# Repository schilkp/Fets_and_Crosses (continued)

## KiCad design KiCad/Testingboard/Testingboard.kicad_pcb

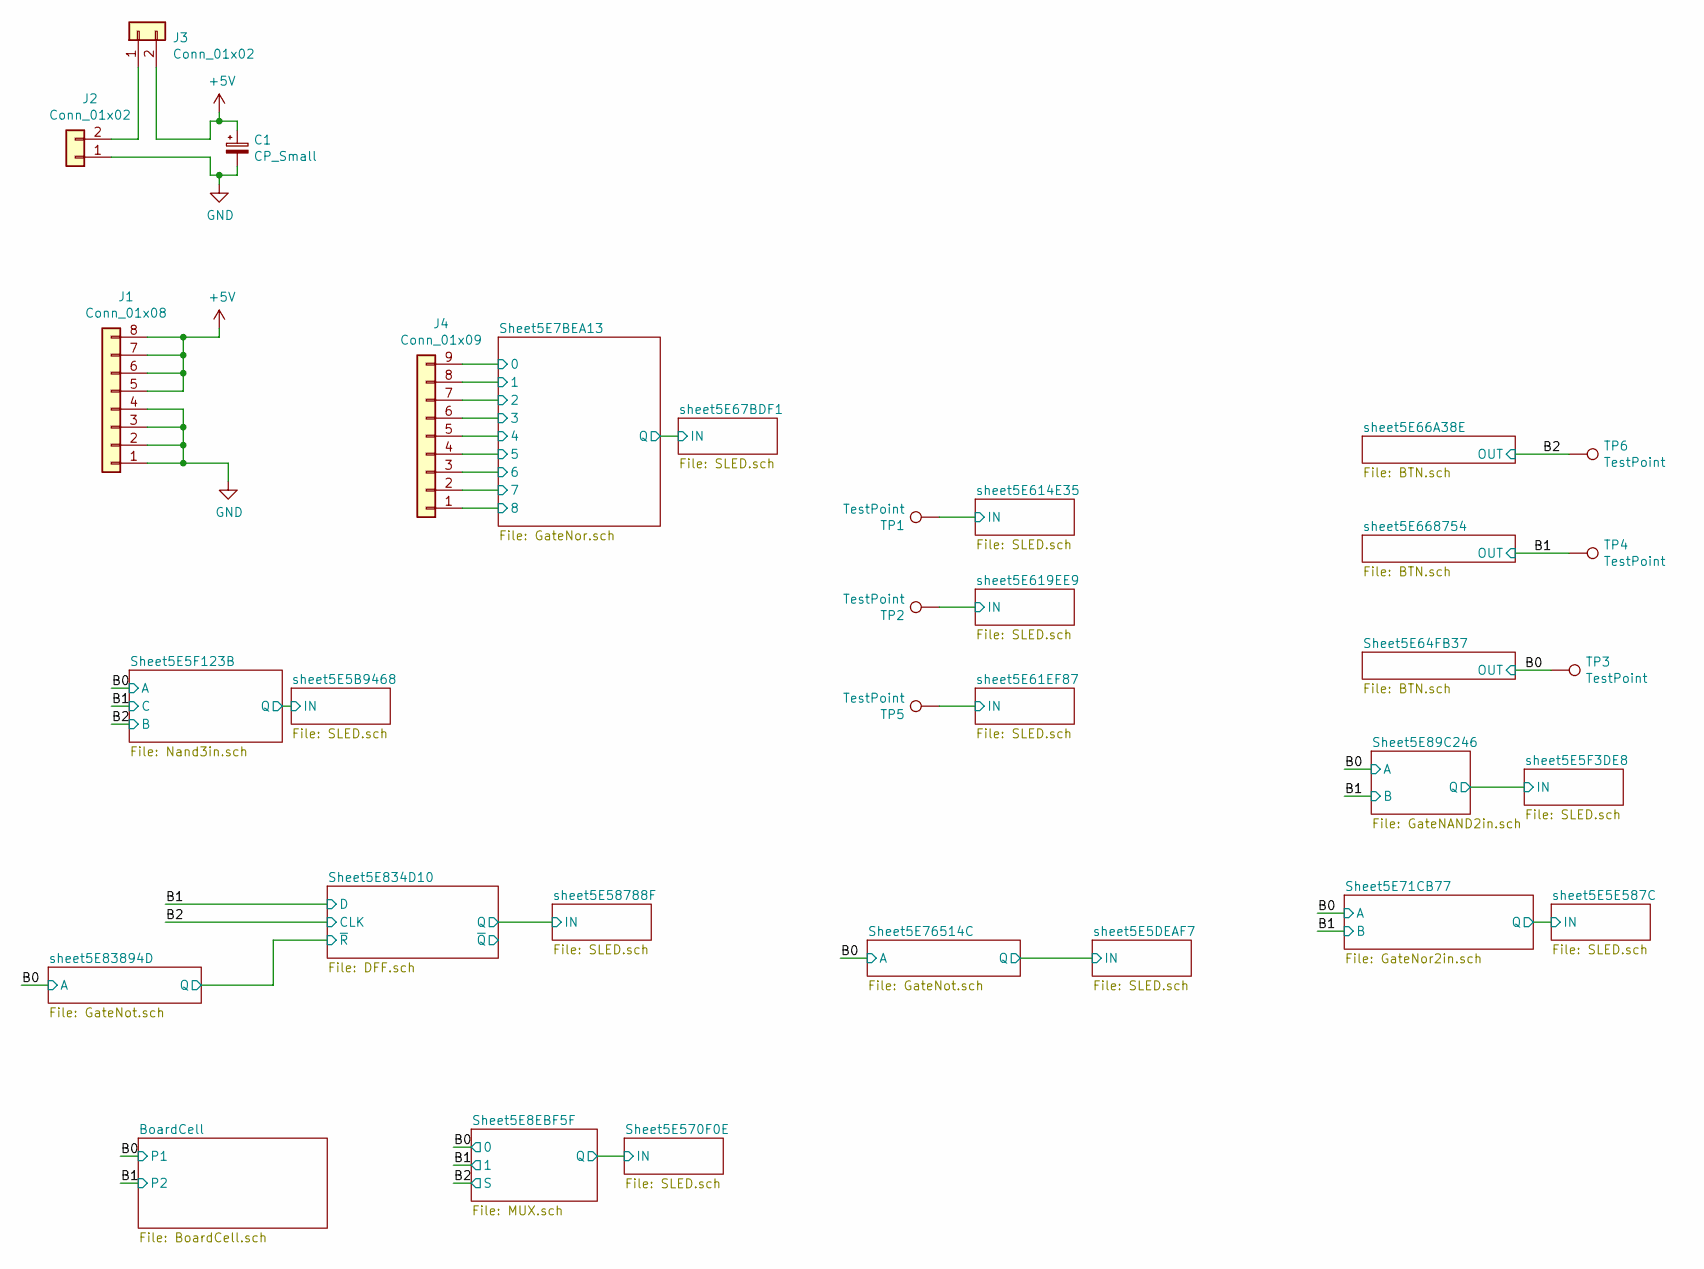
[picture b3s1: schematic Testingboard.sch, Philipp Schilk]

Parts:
C1: CP_Small; CP_Elec_8x6.5
J1: Conn_01x08; PinHeader_1x08_P2.54mm_Vertical
J2, J3: Conn_01x02; PinHeader_1x02_P2.54mm_Vertical
J4: Conn_01x09; PinSocket_1x09_P2.54mm_Vertical
TP1, TP2, TP3, TP4, TP5, TP6: TestPoint; PinSocket_1x01_P2.54mm_Vertical

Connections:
+5V: C1.1, J1.5, J1.6, J1.7, J1.8, J3.2; also elsewhere on the board
/B0: TP3.1; also elsewhere on the board
/B1: TP4.1; also elsewhere on the board
/B2: TP6.1; also elsewhere on the board
/Sheet5E7BEA13/0: J4.9; also elsewhere on the board
/Sheet5E7BEA13/1: J4.8; also elsewhere on the board
/Sheet5E7BEA13/2: J4.7; also elsewhere on the board
/Sheet5E7BEA13/3: J4.6; also elsewhere on the board
/Sheet5E7BEA13/4: J4.5; also elsewhere on the board
/Sheet5E7BEA13/5: J4.4; also elsewhere on the board
/Sheet5E7BEA13/6: J4.3; also elsewhere on the board
/Sheet5E7BEA13/7: J4.2; also elsewhere on the board
/Sheet5E7BEA13/8: J4.1; also elsewhere on the board
/sheet5E61EF87/IN: TP5.1; also elsewhere on the board
/sheet5E614E35/IN: TP1.1; also elsewhere on the board
/sheet5E619EE9/IN: TP2.1; also elsewhere on the board
GND: C1.2, J1.1, J1.2, J1.3, J1.4, J2.1; also elsewhere on the board
unnamed: J2.2, J3.1

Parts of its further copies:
TP21, TP22, TP23: TestPoint; PinSocket_1x01_P2.54mm_Vertical

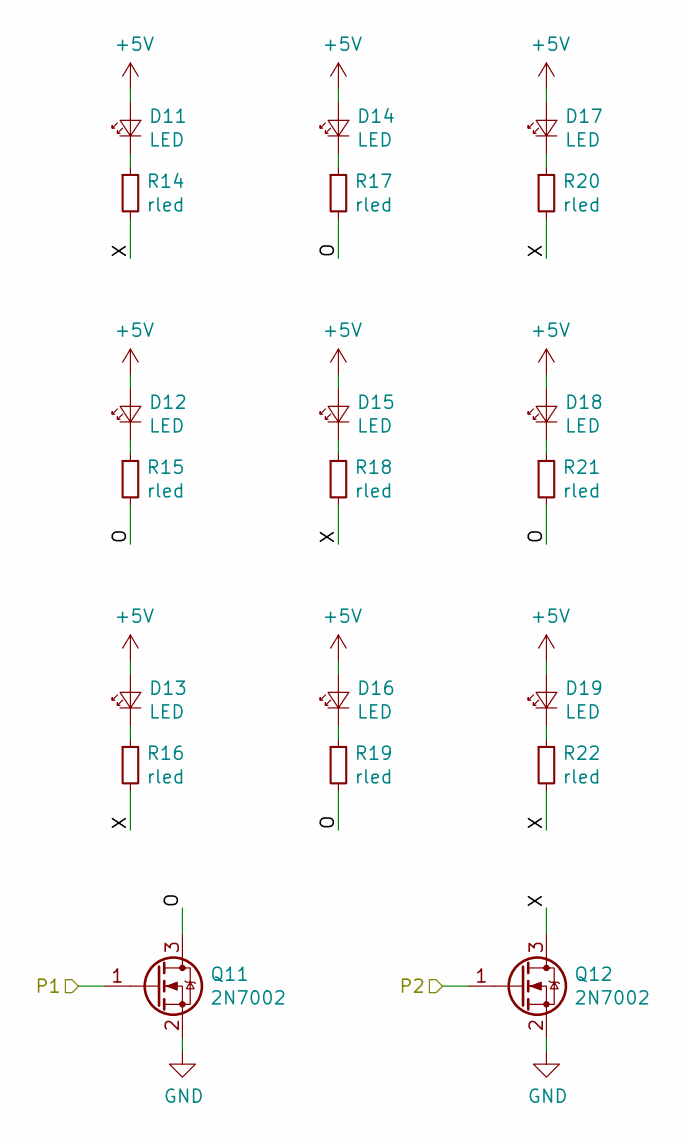
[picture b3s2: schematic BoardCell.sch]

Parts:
D11, D12, D13, D14, D15, D16, D17, D18, D19: LED; LED_0805_2012Metric
Q11, Q12: 2N7002; SOT-23-N
R14, R15, R16, R17, R18, R19, R20, R21, R22: rled; R_0603_1608Metric

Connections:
+5V: D11.2 (A), D12.2 (A), D13.2 (A), D14.2 (A), D15.2 (A), D16.2 (A), D17.2 (A), D18.2 (A), D19.2 (A); also elsewhere on the board
/B0: Q11.1 (G); also elsewhere on the board
/B1: Q12.1 (G); also elsewhere on the board
/BoardCell/O: Q11.3 (D), R15.2, R17.2, R19.2, R21.2
/BoardCell/X: Q12.3 (D), R14.2, R16.2, R18.2, R20.2, R22.2
GND: Q11.2 (S), Q12.2 (S); also elsewhere on the board
unnamed: D11.1 (K), R14.1
unnamed: D12.1 (K), R15.1
unnamed: D13.1 (K), R16.1
unnamed: D14.1 (K), R17.1
unnamed: D15.1 (K), R18.1
unnamed: D16.1 (K), R19.1
unnamed: D17.1 (K), R20.1
unnamed: D18.1 (K), R21.1
unnamed: D19.1 (K), R22.1

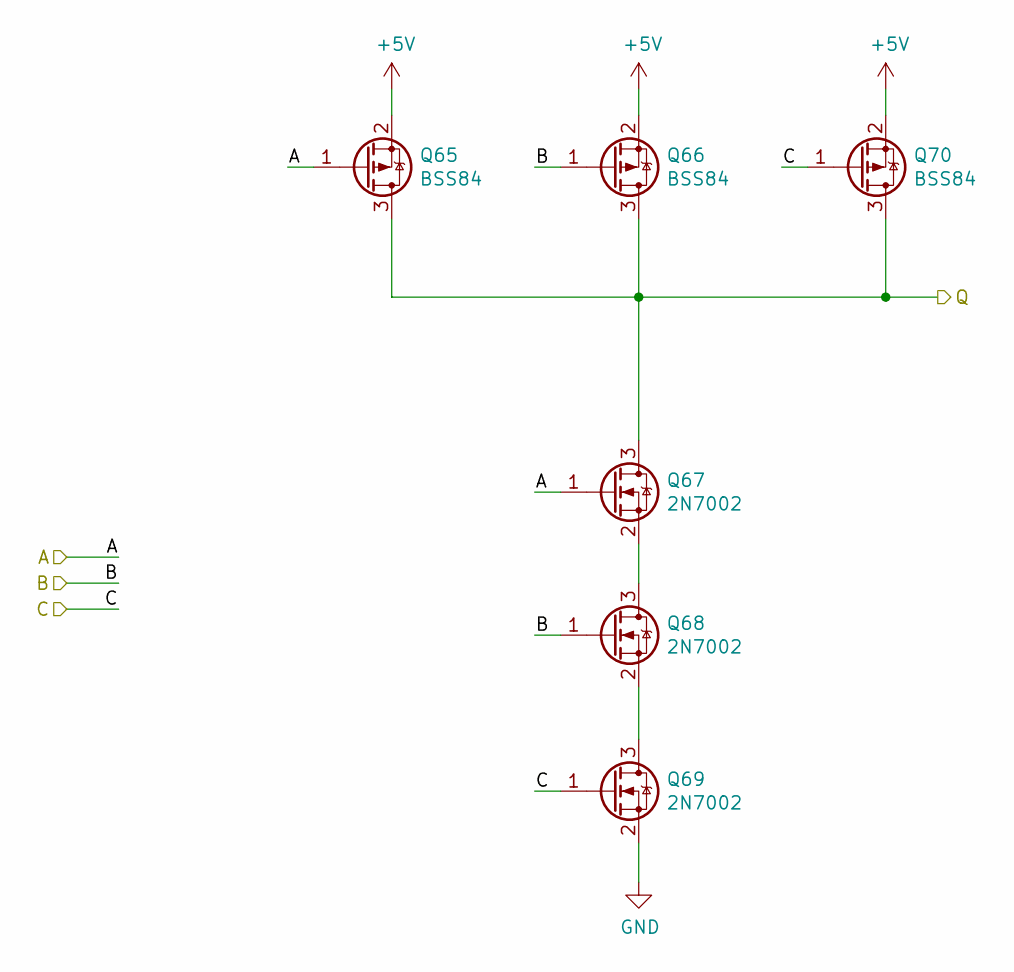
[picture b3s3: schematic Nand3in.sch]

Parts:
Q13, Q14, Q18: BSS84; SOT-23-P
Q15, Q16, Q17: 2N7002; SOT-23-N

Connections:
+5V: Q13.2 (S), Q14.2 (S), Q18.2 (S); also elsewhere on the board
/B0: Q13.1 (G), Q15.1 (G); also elsewhere on the board
/B1: Q17.1 (G), Q18.1 (G); also elsewhere on the board
/B2: Q14.1 (G), Q16.1 (G); also elsewhere on the board
/sheet5E5B9468/IN: Q13.3 (D), Q14.3 (D), Q15.3 (D), Q18.3 (D); also elsewhere on the board
GND: Q17.2 (S); also elsewhere on the board
unnamed: Q15.2 (S), Q16.3 (D)
unnamed: Q16.2 (S), Q17.3 (D)

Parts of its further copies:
Q47, Q48, Q52, Q53, Q54, Q58, Q59, Q60, Q64, Q65, Q66, Q70: BSS84; SOT-23-P
Q49, Q50, Q51, Q55, Q56, Q57, Q61, Q62, Q63, Q67, Q68, Q69: 2N7002; SOT-23-N

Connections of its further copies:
+5V: Q47.2 (S), Q48.2 (S), Q52.2 (S), Q53.2 (S), Q54.2 (S), Q58.2 (S), Q59.2 (S), Q60.2 (S), Q64.2 (S), Q65.2 (S), Q66.2 (S), Q70.2 (S); also elsewhere on the board
/B1: Q60.1 (G), Q62.1 (G); also elsewhere on the board
/B2: Q48.1 (G), Q50.1 (G), Q57.1 (G), Q58.1 (G); also elsewhere on the board
/Sheet5E834D10/sheet5E8D9C76/A: Q54.1 (G), Q56.1 (G), Q59.3 (D), Q60.3 (D), Q61.3 (D), Q64.3 (D); also elsewhere on the board
/Sheet5E834D10/sheet5E8DA6D4/A: Q47.1 (G), Q49.1 (G); also elsewhere on the board
/Sheet5E834D10/sheet5E8DACDC/A: Q47.3 (D), Q48.3 (D), Q49.3 (D), Q52.3 (D), Q53.1 (G), Q55.1 (G); also elsewhere on the board
/Sheet5E834D10/sheet5E8DADBF/A: Q53.3 (D), Q54.3 (D), Q55.3 (D), Q58.3 (D), Q59.1 (G), Q61.1 (G), Q66.1 (G), Q68.1 (G)
/Sheet5E834D10/~Q: Q65.3 (D), Q66.3 (D), Q67.3 (D), Q70.3 (D); also elsewhere on the board
/sheet5E58788F/IN: Q65.1 (G), Q67.1 (G); also elsewhere on the board
/sheet5E83894D/Q: Q51.1 (G), Q52.1 (G), Q63.1 (G), Q64.1 (G), Q69.1 (G), Q70.1 (G); also elsewhere on the board
GND: Q51.2 (S), Q57.2 (S), Q63.2 (S), Q69.2 (S); also elsewhere on the board
unnamed: Q49.2 (S), Q50.3 (D)
unnamed: Q50.2 (S), Q51.3 (D)
unnamed: Q55.2 (S), Q56.3 (D)
unnamed: Q56.2 (S), Q57.3 (D)
unnamed: Q61.2 (S), Q62.3 (D)
unnamed: Q62.2 (S), Q63.3 (D)
unnamed: Q67.2 (S), Q68.3 (D)
unnamed: Q68.2 (S), Q69.3 (D)

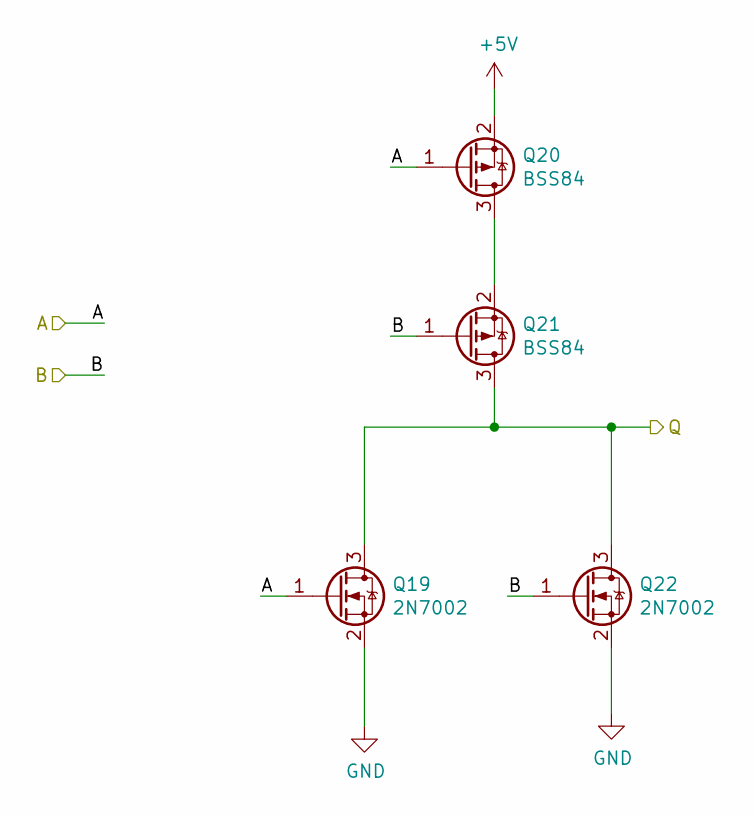
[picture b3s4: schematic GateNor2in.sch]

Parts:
Q19, Q22: 2N7002; SOT-23-N
Q20, Q21: BSS84; SOT-23-P

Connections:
+5V: Q20.2 (S); also elsewhere on the board
/B0: Q19.1 (G), Q20.1 (G); also elsewhere on the board
/B1: Q21.1 (G), Q22.1 (G); also elsewhere on the board
/sheet5E5E587C/IN: Q19.3 (D), Q21.3 (D), Q22.3 (D); also elsewhere on the board
GND: Q19.2 (S), Q22.2 (S); also elsewhere on the board
unnamed: Q20.3 (D), Q21.2 (S)

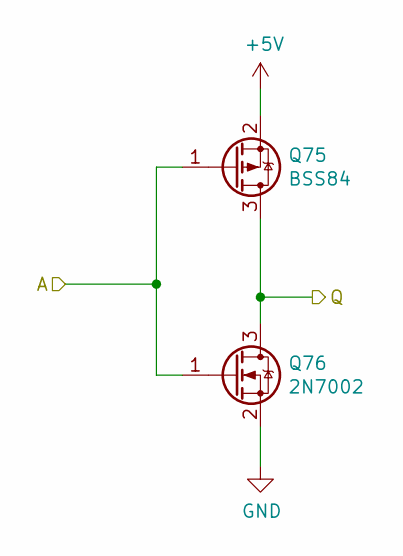
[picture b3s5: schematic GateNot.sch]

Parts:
Q23: BSS84; SOT-23-P
Q24: 2N7002; SOT-23-N

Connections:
+5V: Q23.2 (S); also elsewhere on the board
/B0: Q23.1 (G), Q24.1 (G); also elsewhere on the board
/sheet5E5DEAF7/IN: Q23.3 (D), Q24.3 (D); also elsewhere on the board
GND: Q24.2 (S); also elsewhere on the board

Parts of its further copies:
Q75, Q85: BSS84; SOT-23-P
Q76, Q86: 2N7002; SOT-23-N

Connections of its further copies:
+5V: Q75.2 (S), Q85.2 (S); also elsewhere on the board
/B0: Q75.1 (G), Q76.1 (G); also elsewhere on the board
/B2: Q85.1 (G), Q86.1 (G); also elsewhere on the board
/Sheet5E8EBF5F/sheet5E900E63/Q: Q85.3 (D), Q86.3 (D); also elsewhere on the board
/sheet5E83894D/Q: Q75.3 (D), Q76.3 (D); also elsewhere on the board
GND: Q76.2 (S), Q86.2 (S); also elsewhere on the board

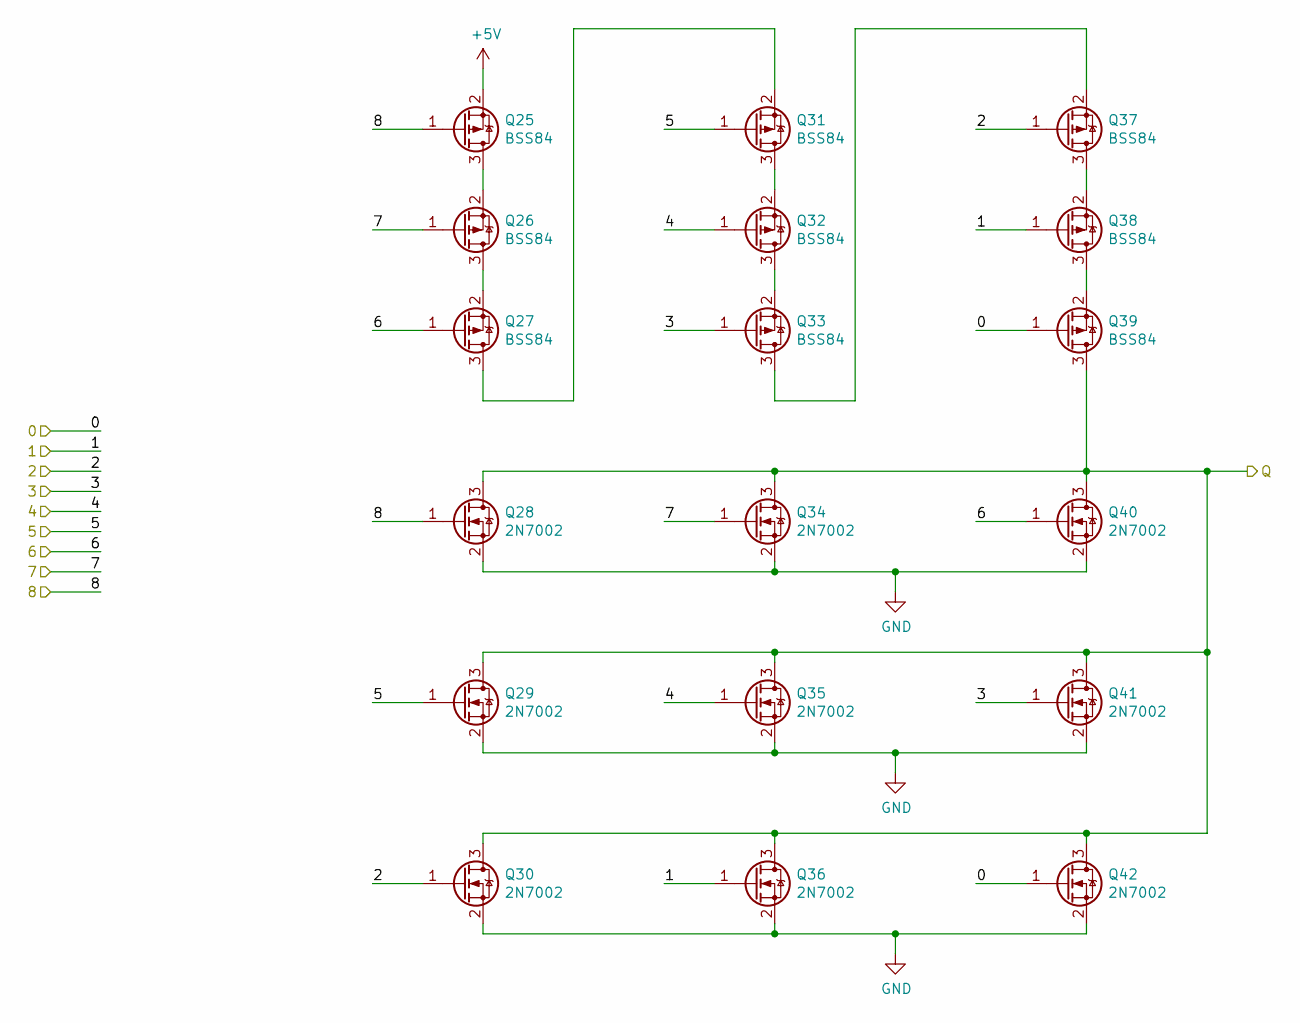
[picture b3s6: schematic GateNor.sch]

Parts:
Q25, Q26, Q27, Q31, Q32, Q33, Q37, Q38, Q39: BSS84; SOT-23-P
Q28, Q29, Q30, Q34, Q35, Q36, Q40, Q41, Q42: 2N7002; SOT-23-N

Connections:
+5V: Q25.2 (S); also elsewhere on the board
/Sheet5E7BEA13/0: Q39.1 (G), Q42.1 (G); also elsewhere on the board
/Sheet5E7BEA13/1: Q36.1 (G), Q38.1 (G); also elsewhere on the board
/Sheet5E7BEA13/2: Q30.1 (G), Q37.1 (G); also elsewhere on the board
/Sheet5E7BEA13/3: Q33.1 (G), Q41.1 (G); also elsewhere on the board
/Sheet5E7BEA13/4: Q32.1 (G), Q35.1 (G); also elsewhere on the board
/Sheet5E7BEA13/5: Q29.1 (G), Q31.1 (G); also elsewhere on the board
/Sheet5E7BEA13/6: Q27.1 (G), Q40.1 (G); also elsewhere on the board
/Sheet5E7BEA13/7: Q26.1 (G), Q34.1 (G); also elsewhere on the board
/Sheet5E7BEA13/8: Q25.1 (G), Q28.1 (G); also elsewhere on the board
/sheet5E67BDF1/IN: Q28.3 (D), Q29.3 (D), Q30.3 (D), Q34.3 (D), Q35.3 (D), Q36.3 (D), Q39.3 (D), Q40.3 (D), Q41.3 (D), Q42.3 (D); also elsewhere on the board
GND: Q28.2 (S), Q29.2 (S), Q30.2 (S), Q34.2 (S), Q35.2 (S), Q36.2 (S), Q40.2 (S), Q41.2 (S), Q42.2 (S); also elsewhere on the board
unnamed: Q25.3 (D), Q26.2 (S)
unnamed: Q26.3 (D), Q27.2 (S)
unnamed: Q27.3 (D), Q31.2 (S)
unnamed: Q31.3 (D), Q32.2 (S)
unnamed: Q32.3 (D), Q33.2 (S)
unnamed: Q33.3 (D), Q37.2 (S)
unnamed: Q37.3 (D), Q38.2 (S)
unnamed: Q38.3 (D), Q39.2 (S)

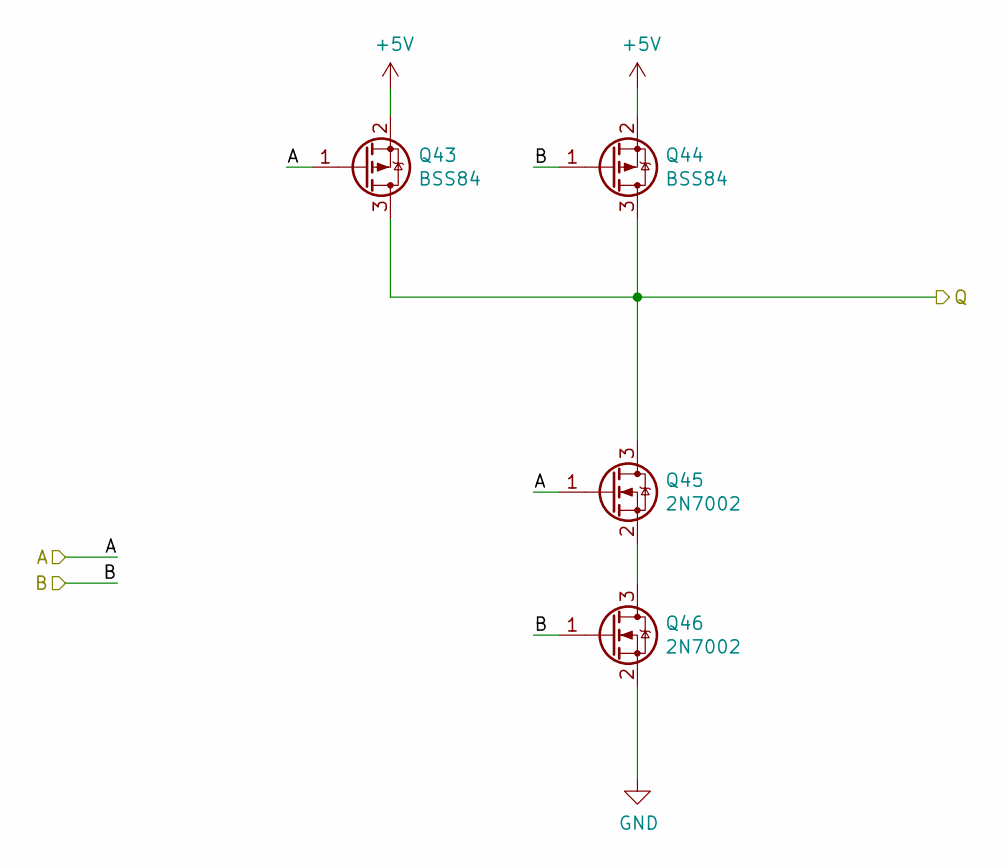
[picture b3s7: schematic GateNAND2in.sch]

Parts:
Q43, Q44: BSS84; SOT-23-P
Q45, Q46: 2N7002; SOT-23-N

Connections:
+5V: Q43.2 (S), Q44.2 (S); also elsewhere on the board
/Sheet5E834D10/sheet5E8D9C76/A: Q43.1 (G), Q45.1 (G); also elsewhere on the board
/Sheet5E834D10/sheet5E8DA6D4/A: Q43.3 (D), Q44.3 (D), Q45.3 (D); also elsewhere on the board
/Sheet5E834D10/sheet5E8DACDC/A: Q44.1 (G), Q46.1 (G); also elsewhere on the board
GND: Q46.2 (S); also elsewhere on the board
unnamed: Q45.2 (S), Q46.3 (D)

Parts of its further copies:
Q71, Q72, Q77, Q78: BSS84; SOT-23-P
Q73, Q74, Q79, Q80: 2N7002; SOT-23-N

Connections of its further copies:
+5V: Q71.2 (S), Q72.2 (S), Q77.2 (S), Q78.2 (S); also elsewhere on the board
/B0: Q77.1 (G), Q79.1 (G); also elsewhere on the board
/B1: Q78.1 (G), Q80.1 (G); also elsewhere on the board
/Sheet5E834D10/sheet5E8DACDC/A: Q71.1 (G), Q73.1 (G); also elsewhere on the board
/Sheet5E834D10/~Q: Q72.1 (G), Q74.1 (G); also elsewhere on the board
/sheet5E5F3DE8/IN: Q77.3 (D), Q78.3 (D), Q79.3 (D); also elsewhere on the board
/sheet5E58788F/IN: Q71.3 (D), Q72.3 (D), Q73.3 (D); also elsewhere on the board
GND: Q74.2 (S), Q80.2 (S); also elsewhere on the board
unnamed: Q73.2 (S), Q74.3 (D)
unnamed: Q79.2 (S), Q80.3 (D)

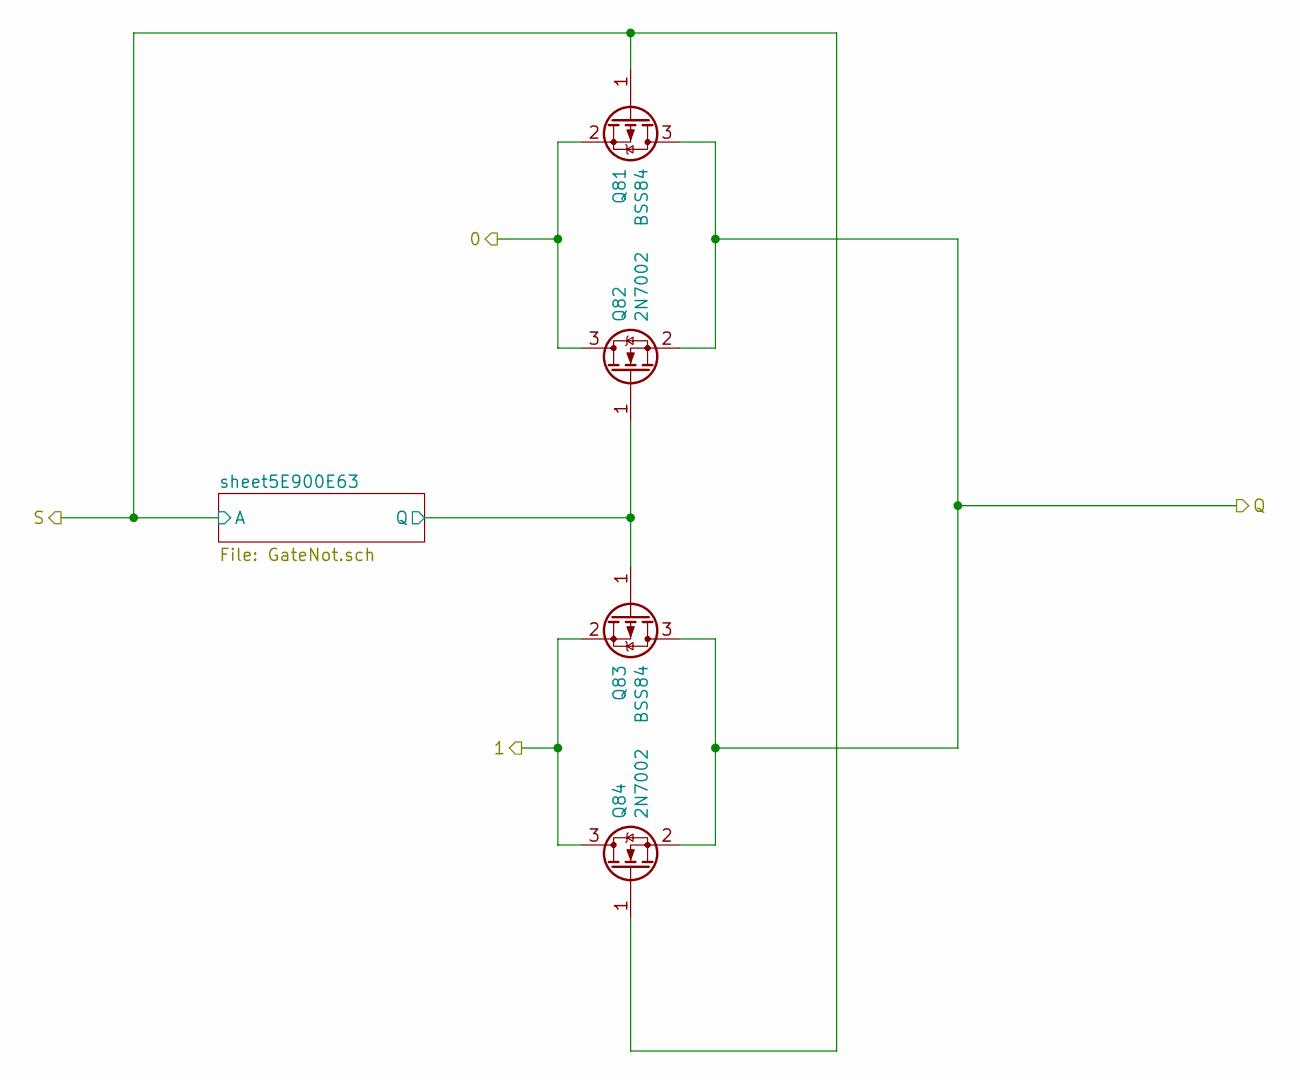
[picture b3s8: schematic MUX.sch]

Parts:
Q81, Q83: BSS84; SOT-23-P
Q82, Q84: 2N7002; SOT-23-N

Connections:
/B0: Q81.2 (S), Q82.3 (D); also elsewhere on the board
/B1: Q83.2 (S), Q84.3 (D); also elsewhere on the board
/B2: Q81.1 (G), Q84.1 (G); also elsewhere on the board
/Sheet5E8EBF5F/sheet5E900E63/Q: Q82.1 (G), Q83.1 (G); also elsewhere on the board
/Sheet5E570F0E/IN: Q81.3 (D), Q82.2 (S), Q83.3 (D), Q84.2 (S); also elsewhere on the board

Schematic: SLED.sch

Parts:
D1: LED_Small; LED_0805_2012Metric
Q1: 2N7002; SOT-23-N
R1: R_Small; R_0603_1608Metric

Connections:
+5V: R1.1; also elsewhere on the board
/Sheet5E570F0E/IN: Q1.1 (G); also elsewhere on the board
GND: Q1.2 (S); also elsewhere on the board
unnamed: D1.1 (K), Q1.3 (D)
unnamed: D1.2 (A), R1.2

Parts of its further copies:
D2, D3, D4, D5, D6, D7, D8, D9, D10: LED_Small; LED_0805_2012Metric
Q2, Q3, Q4, Q5, Q6, Q7, Q8, Q9, Q10: 2N7002; SOT-23-N
R2, R3, R4, R5, R6, R7, R8, R9, R13: R_Small; R_0603_1608Metric

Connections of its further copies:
+5V: R2.1, R3.1, R4.1, R5.1, R6.1, R7.1, R8.1, R9.1, R13.1; also elsewhere on the board
/sheet5E5B9468/IN: Q3.1 (G); also elsewhere on the board
/sheet5E5DEAF7/IN: Q4.1 (G); also elsewhere on the board
/sheet5E5E587C/IN: Q5.1 (G); also elsewhere on the board
/sheet5E5F3DE8/IN: Q6.1 (G); also elsewhere on the board
/sheet5E61EF87/IN: Q9.1 (G); also elsewhere on the board
/sheet5E67BDF1/IN: Q10.1 (G); also elsewhere on the board
/sheet5E614E35/IN: Q7.1 (G); also elsewhere on the board
/sheet5E619EE9/IN: Q8.1 (G); also elsewhere on the board
/sheet5E58788F/IN: Q2.1 (G); also elsewhere on the board
GND: Q2.2 (S), Q3.2 (S), Q4.2 (S), Q5.2 (S), Q6.2 (S), Q7.2 (S), Q8.2 (S), Q9.2 (S), Q10.2 (S); also elsewhere on the board
unnamed: D2.1 (K), Q2.3 (D)
unnamed: D2.2 (A), R2.2
unnamed: D3.1 (K), Q3.3 (D)
unnamed: D3.2 (A), R3.2
unnamed: D4.1 (K), Q4.3 (D)
unnamed: D4.2 (A), R4.2
unnamed: D5.1 (K), Q5.3 (D)
unnamed: D5.2 (A), R5.2
unnamed: D6.1 (K), Q6.3 (D)
unnamed: D6.2 (A), R6.2
unnamed: D7.1 (K), Q7.3 (D)
unnamed: D7.2 (A), R7.2
unnamed: D8.1 (K), Q8.3 (D)
unnamed: D8.2 (A), R8.2
unnamed: D9.1 (K), Q9.3 (D)
unnamed: D9.2 (A), R9.2
unnamed: D10.1 (K), Q10.3 (D)
unnamed: D10.2 (A), R13.2

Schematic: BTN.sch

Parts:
C2: C_Small; C_0603_1608Metric
R10: R_Small; R_0603_1608Metric
SW1: SW_Push; SW_PUSH_6mm
U1: 74LVC1G125; SOT-353_SC-70-5

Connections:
+5V: SW1.1, U1.5 (VCC); also elsewhere on the board
/B0: U1.4; also elsewhere on the board
GND: C2.1, R10.2, U1.1, U1.3 (GND); also elsewhere on the board
unnamed: C2.2, R10.1, SW1.2, U1.2

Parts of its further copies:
C3, C4: C_Small; C_0603_1608Metric
R11, R12: R_Small; R_0603_1608Metric
SW2, SW3: SW_Push; SW_PUSH_6mm
U2, U3: 74LVC1G125; SOT-353_SC-70-5

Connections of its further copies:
+5V: SW2.1, SW3.1, U2.5 (VCC), U3.5 (VCC); also elsewhere on the board
/B1: U2.4; also elsewhere on the board
/B2: U3.4; also elsewhere on the board
GND: C3.1, C4.1, R11.2, R12.2, U2.1, U2.3 (GND), U3.1, U3.3 (GND); also elsewhere on the board
unnamed: C3.2, R11.1, SW2.2, U2.2
unnamed: C4.2, R12.1, SW3.2, U3.2

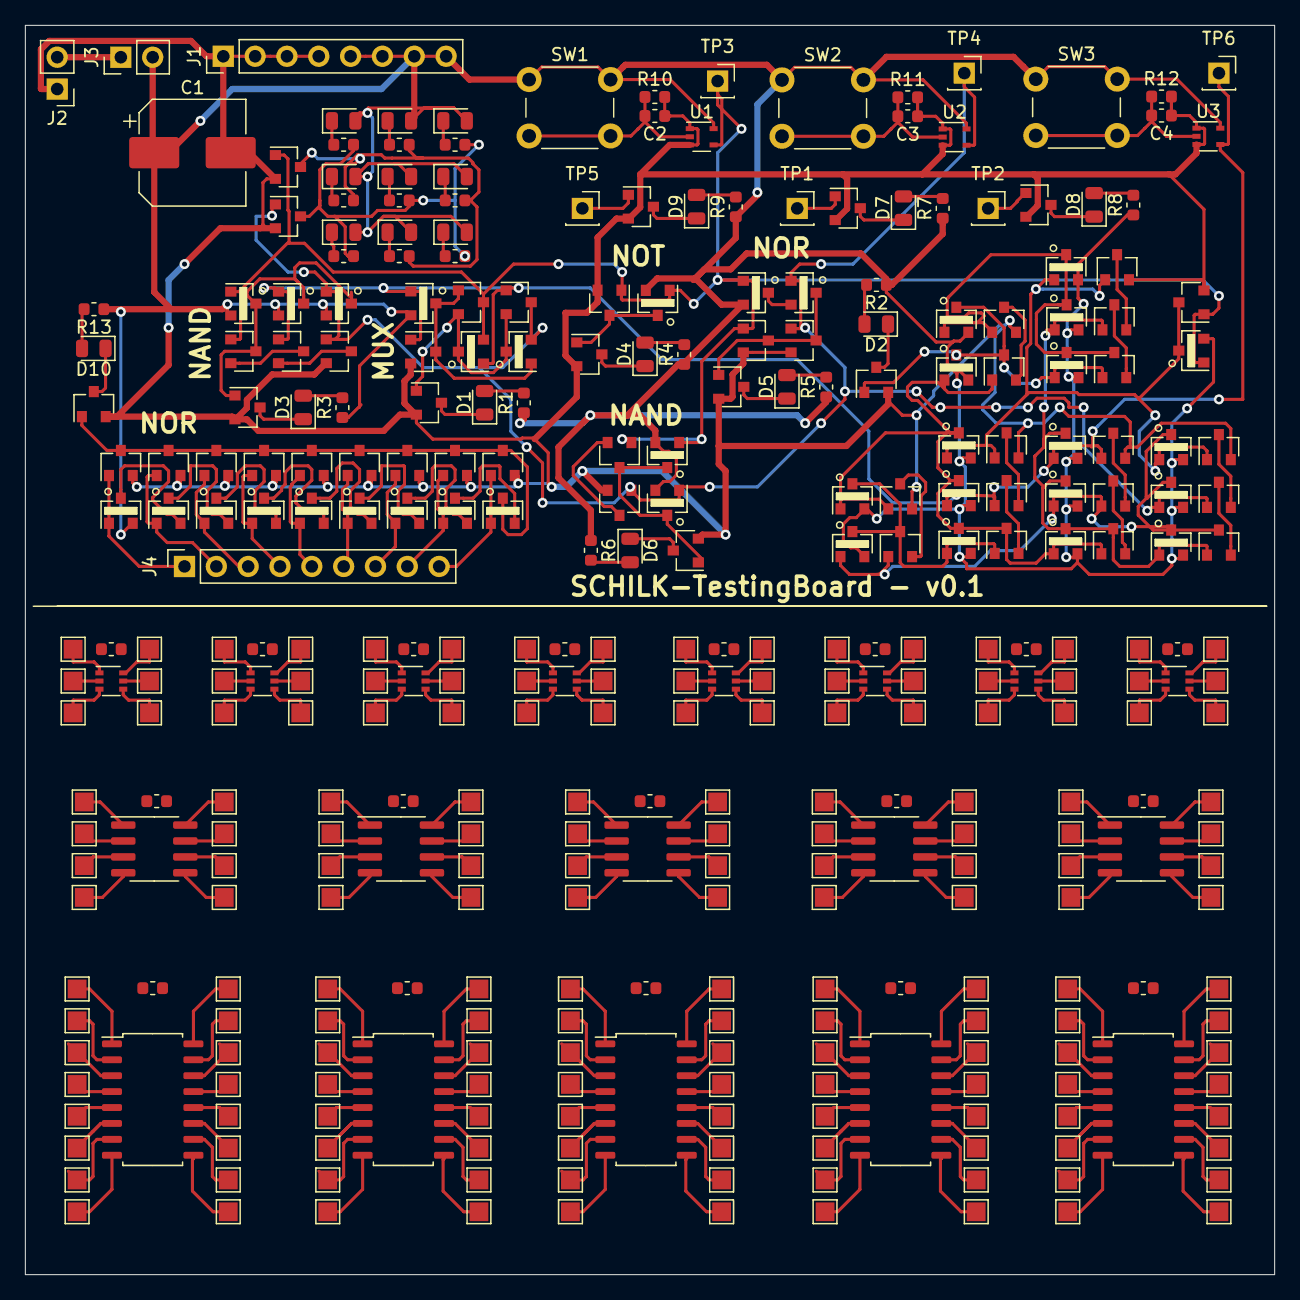
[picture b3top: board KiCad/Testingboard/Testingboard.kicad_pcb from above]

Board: 2 copper layers, 99.7 x 99.7 mm, 148 parts (0 on the bottom side), 88 nets.

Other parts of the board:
e: SOIC-8_3.9x4.9mm_P1.27mm

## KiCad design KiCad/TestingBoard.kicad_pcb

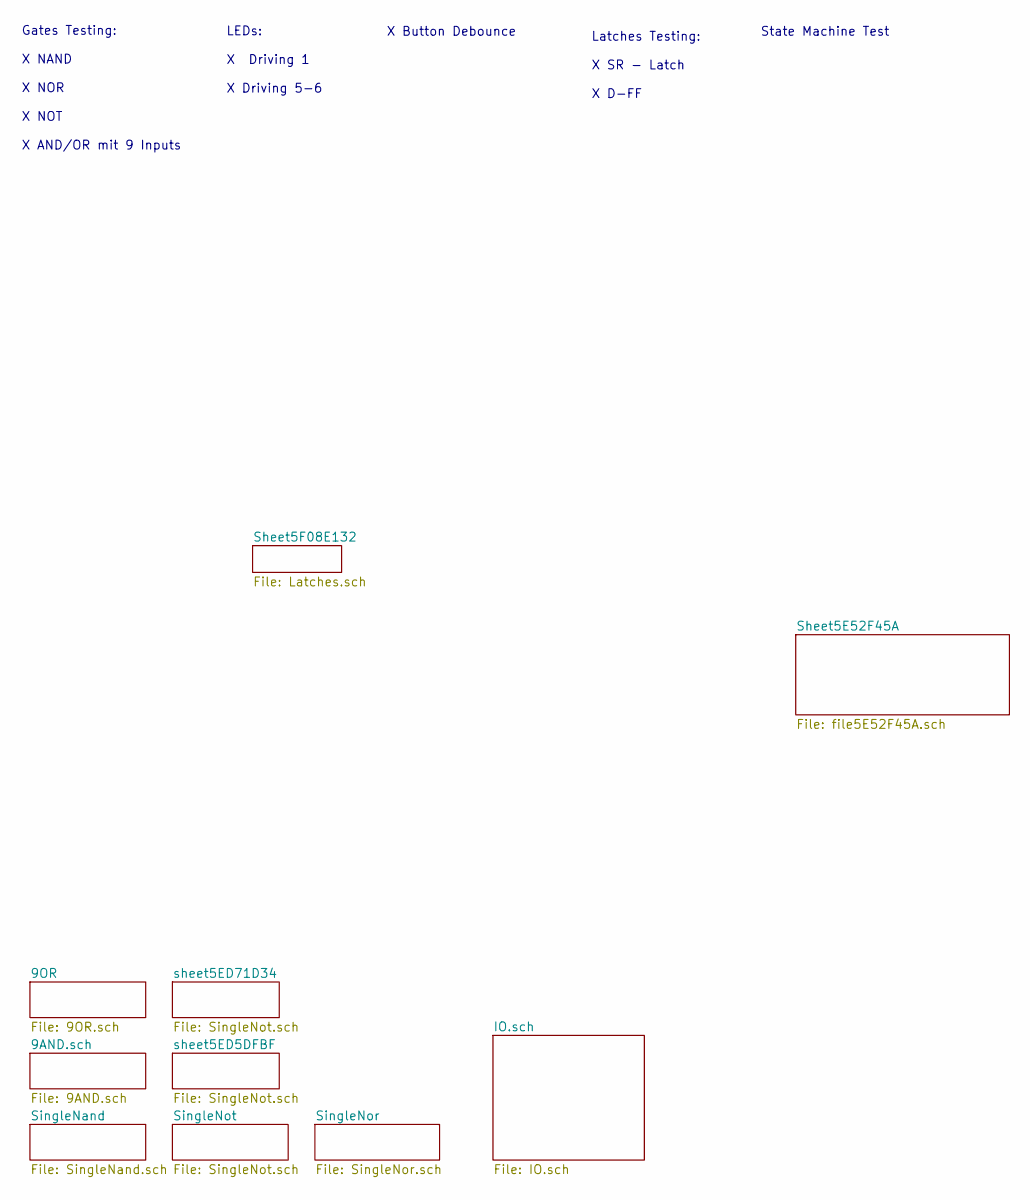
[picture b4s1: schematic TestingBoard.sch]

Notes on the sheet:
Gates Testing: X NAND X NOR X NOT X AND/OR mit 9 Inputs
Latches Testing: X SR - Latch X D-FF
LEDs: X Driving 1 X Driving 5-6
X Button Debounce
State Machine Test

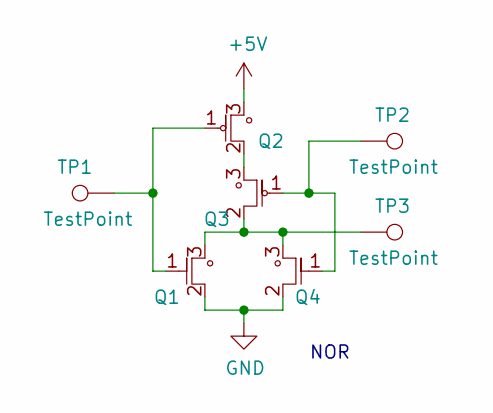
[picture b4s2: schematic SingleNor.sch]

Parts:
Q1, Q4: NM; SOT-23-N
Q2, Q3: PM; SOT-23-P
TP1, TP2, TP3: TestPoint; PinSocket_1x01_P2.54mm_Vertical

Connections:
+5V: Q2.3; also elsewhere on the board
GND: Q1.2, Q4.2; also elsewhere on the board
unnamed: Q1.1, Q2.1, TP1.1
unnamed: Q1.3, Q3.2, Q4.3, TP3.1
unnamed: Q2.2, Q3.3
unnamed: Q3.1, Q4.1, TP2.1

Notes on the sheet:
NOR

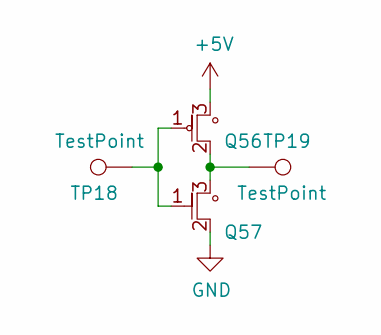
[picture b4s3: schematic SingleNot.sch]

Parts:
Q5: PM; SOT-23-P
Q6: NM; SOT-23-N
TP4, TP5: TestPoint; PinSocket_1x01_P2.54mm_Vertical

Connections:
+5V: Q5.3; also elsewhere on the board
GND: Q6.2; also elsewhere on the board
unnamed: Q5.1, Q6.1, TP4.1
unnamed: Q5.2, Q6.3, TP5.1

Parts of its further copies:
Q54, Q56: PM; SOT-23-P
Q55, Q57: NM; SOT-23-N
TP16, TP17, TP18, TP19: TestPoint; PinSocket_1x01_P2.54mm_Vertical

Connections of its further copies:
+5V: Q54.3, Q56.3; also elsewhere on the board
GND: Q55.2, Q57.2; also elsewhere on the board
unnamed: Q54.1, Q55.1, TP16.1
unnamed: Q54.2, Q55.3, TP17.1
unnamed: Q56.1, Q57.1, TP18.1
unnamed: Q56.2, Q57.3, TP19.1

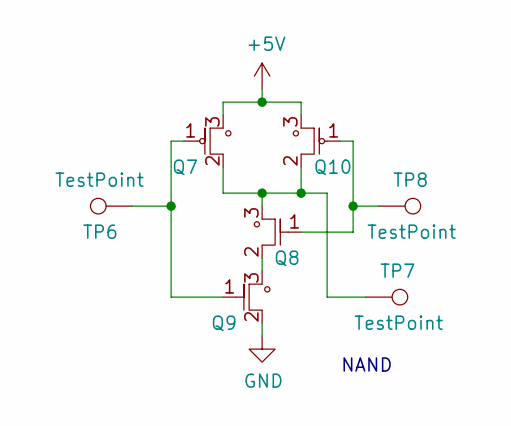
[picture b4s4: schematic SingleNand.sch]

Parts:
Q7, Q10: PM; SOT-23-P
Q8, Q9: NM; SOT-23-N
TP6, TP7, TP8: TestPoint; PinSocket_1x01_P2.54mm_Vertical

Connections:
+5V: Q7.3, Q10.3; also elsewhere on the board
GND: Q9.2; also elsewhere on the board
unnamed: Q7.1, Q9.1, TP6.1
unnamed: Q8.2, Q9.3
unnamed: Q8.1, Q10.1, TP8.1
unnamed: Q7.2, Q8.3, Q10.2, TP7.1

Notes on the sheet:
NAND

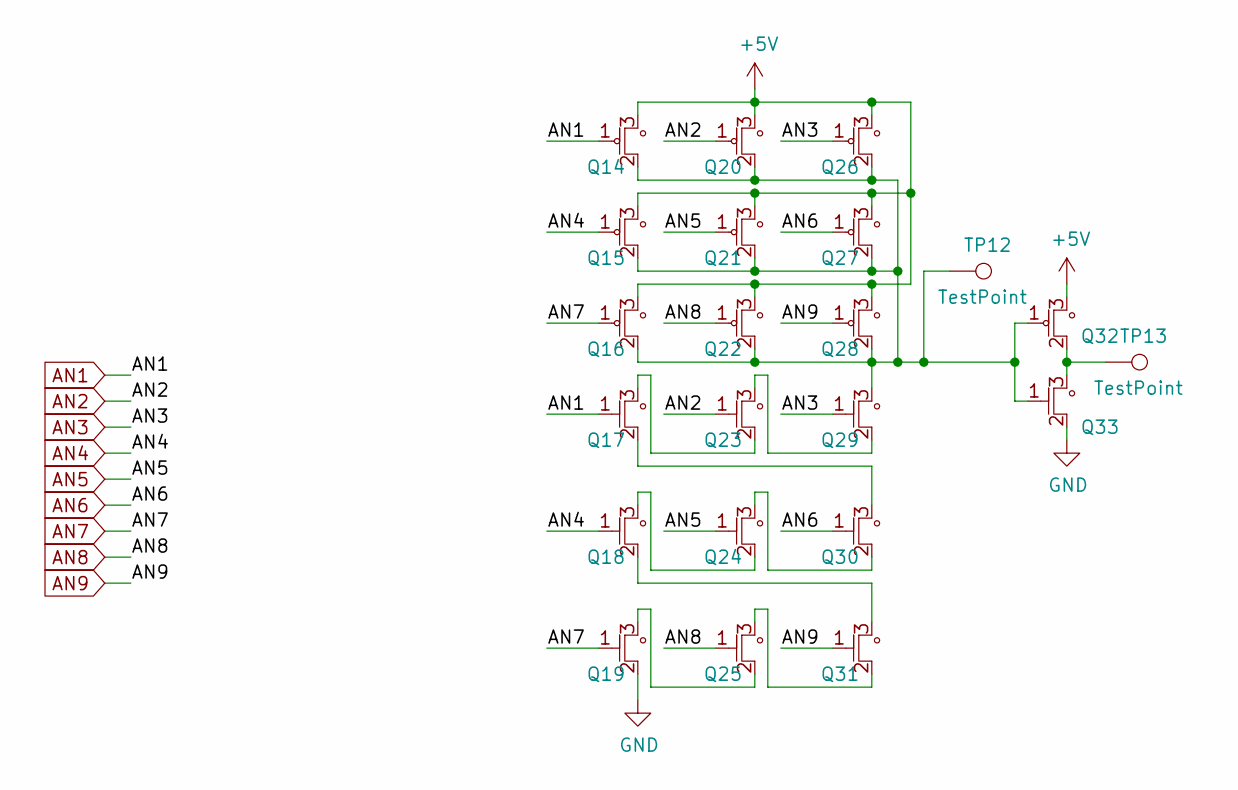
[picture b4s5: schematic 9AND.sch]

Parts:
Q14, Q15, Q16, Q20, Q21, Q22, Q26, Q27, Q28, Q32: PM; SOT-23-P
Q17, Q18, Q19, Q23, Q24, Q25, Q29, Q30, Q31, Q33: NM; SOT-23-N
TP12, TP13: TestPoint; PinSocket_1x01_P2.54mm_Vertical

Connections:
+5V: Q14.3, Q15.3, Q16.3, Q20.3, Q21.3, Q22.3, Q26.3, Q27.3, Q28.3, Q32.3; also elsewhere on the board
AN1: Q14.1, Q17.1; also elsewhere on the board
AN2: Q20.1, Q23.1; also elsewhere on the board
AN3: Q26.1, Q29.1; also elsewhere on the board
AN4: Q15.1, Q18.1; also elsewhere on the board
AN5: Q21.1, Q24.1; also elsewhere on the board
AN6: Q27.1, Q30.1; also elsewhere on the board
AN7: Q16.1, Q19.1; also elsewhere on the board
AN8: Q22.1, Q25.1; also elsewhere on the board
AN9: Q28.1, Q31.1; also elsewhere on the board
GND: Q19.2, Q33.2; also elsewhere on the board
unnamed: Q14.2, Q15.2, Q16.2, Q20.2, Q21.2, Q22.2, Q26.2, Q27.2, Q28.2, Q29.3, Q32.1, Q33.1, TP12.1
unnamed: Q17.2, Q30.3
unnamed: Q17.3, Q23.2
unnamed: Q18.2, Q31.3
unnamed: Q18.3, Q24.2
unnamed: Q19.3, Q25.2
unnamed: Q23.3, Q29.2
unnamed: Q24.3, Q30.2
unnamed: Q25.3, Q31.2
unnamed: Q32.2, Q33.3, TP13.1

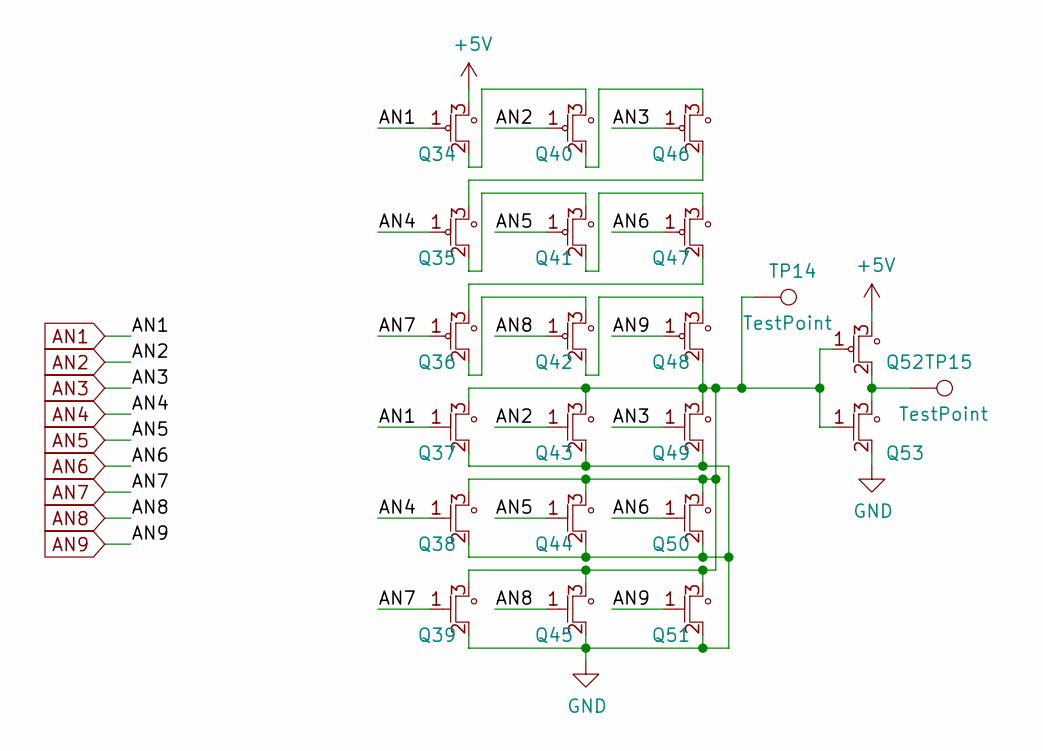
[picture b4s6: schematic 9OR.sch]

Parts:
Q34, Q35, Q36, Q40, Q41, Q42, Q46, Q47, Q48, Q52: PM; SOT-23-P
Q37, Q38, Q39, Q43, Q44, Q45, Q49, Q50, Q51, Q53: NM; SOT-23-N
TP14, TP15: TestPoint; PinSocket_1x01_P2.54mm_Vertical

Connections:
+5V: Q34.3, Q52.3; also elsewhere on the board
AN1: Q34.1, Q37.1; also elsewhere on the board
AN2: Q40.1, Q43.1; also elsewhere on the board
AN3: Q46.1, Q49.1; also elsewhere on the board
AN4: Q35.1, Q38.1; also elsewhere on the board
AN5: Q41.1, Q44.1; also elsewhere on the board
AN6: Q47.1, Q50.1; also elsewhere on the board
AN7: Q36.1, Q39.1; also elsewhere on the board
AN8: Q42.1, Q45.1; also elsewhere on the board
AN9: Q48.1, Q51.1; also elsewhere on the board
GND: Q37.2, Q38.2, Q39.2, Q43.2, Q44.2, Q45.2, Q49.2, Q50.2, Q51.2, Q53.2; also elsewhere on the board
unnamed: Q34.2, Q40.3
unnamed: Q35.2, Q41.3
unnamed: Q35.3, Q46.2
unnamed: Q36.2, Q42.3
unnamed: Q36.3, Q47.2
unnamed: Q37.3, Q38.3, Q39.3, Q43.3, Q44.3, Q45.3, Q48.2, Q49.3, Q50.3, Q51.3, Q52.1, Q53.1, TP14.1
unnamed: Q40.2, Q46.3
unnamed: Q41.2, Q47.3
unnamed: Q42.2, Q48.3
unnamed: Q52.2, Q53.3, TP15.1
